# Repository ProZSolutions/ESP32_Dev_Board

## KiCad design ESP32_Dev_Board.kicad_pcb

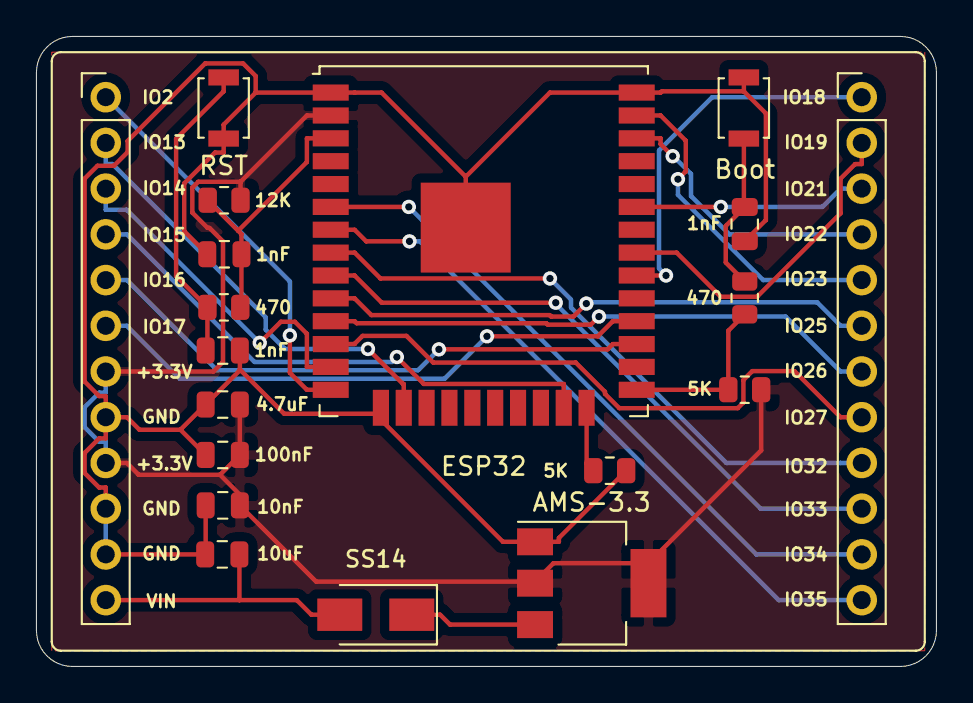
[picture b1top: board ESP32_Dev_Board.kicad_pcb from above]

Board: 2 copper layers, 50.0 x 35.0 mm, 19 parts (0 on the bottom side), 27 nets.

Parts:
1nF, 1nF#2, 1nF#3: 1nF; C_0805_2012Metric
4.7uF: 4.7uF; C_0805_2012Metric
5K, 5K#2: 5K; R_0805_2012Metric
10nF: 10nF; C_0805_2012Metric
10uF: 10uF; C_0805_2012Metric
12K: 12K; R_0805_2012Metric
100nF: 100nF; C_0805_2012Metric
470, 470#2: 470; R_0805_2012Metric
AMS-3.3: AMS1117-3.3; SOT-223-3_TabPin2
Boot: SW_SPST; SW_SPST_B3U-1000P
ESP32: ESP32-WROOM-32U
J1, J2: Conn_01x12; PinHeader_1x12_P2.54mm_Vertical
RST: SW_SPST; SW_SPST_B3U-1000P
SS14: D_Schottky; D_SMA

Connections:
+3V3: 4.7uF.1, 5K.2, 10nF.1, 12K.2, 100nF.1, AMS-3.3.2, ESP32.2, J1.7, J1.9
EN: 1nF.2, 12K.1, 470.1, ESP32.3
GND: 1nF.1, 1nF#2.2, 1nF#3.2, 4.7uF.2, 5K#2.1, 10nF.2, 10uF.2, 100nF.2, AMS-3.3.1, Boot.1, ESP32.1, ESP32.15, ESP32.38, ESP32.39, J1.8, J1.10, J1.11, RST.1
IO0: 5K.1, 470#2.1, ESP32.25
IO2: 5K#2.2, ESP32.24
IO12: ESP32.14, J1.1
IO13: ESP32.16, J1.2
IO14: ESP32.13, J1.3
IO15: ESP32.23, J1.4
IO16: ESP32.27, J1.5
IO17: ESP32.28, J1.6
IO18: ESP32.30, J2.1
IO19: ESP32.31, J2.2
IO21: ESP32.33, J2.3
IO22: ESP32.36, J2.4
IO23: ESP32.37, J2.5
IO25: ESP32.10, J2.6
IO26: ESP32.11, J2.7
IO27: ESP32.12, J2.8
IO32: ESP32.8, J2.9
IO33: ESP32.9, J2.10
IO34: ESP32.6, J2.11
IO35: ESP32.7, J2.12
unnamed: 1nF#2.1, 470.2, RST.2
unnamed: 1nF#3.1, 470#2.2, Boot.2
unnamed: AMS-3.3.3, SS14.1
VIN: 10uF.1, J1.12, SS14.2

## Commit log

2021-07-15 Change 3D Picture
